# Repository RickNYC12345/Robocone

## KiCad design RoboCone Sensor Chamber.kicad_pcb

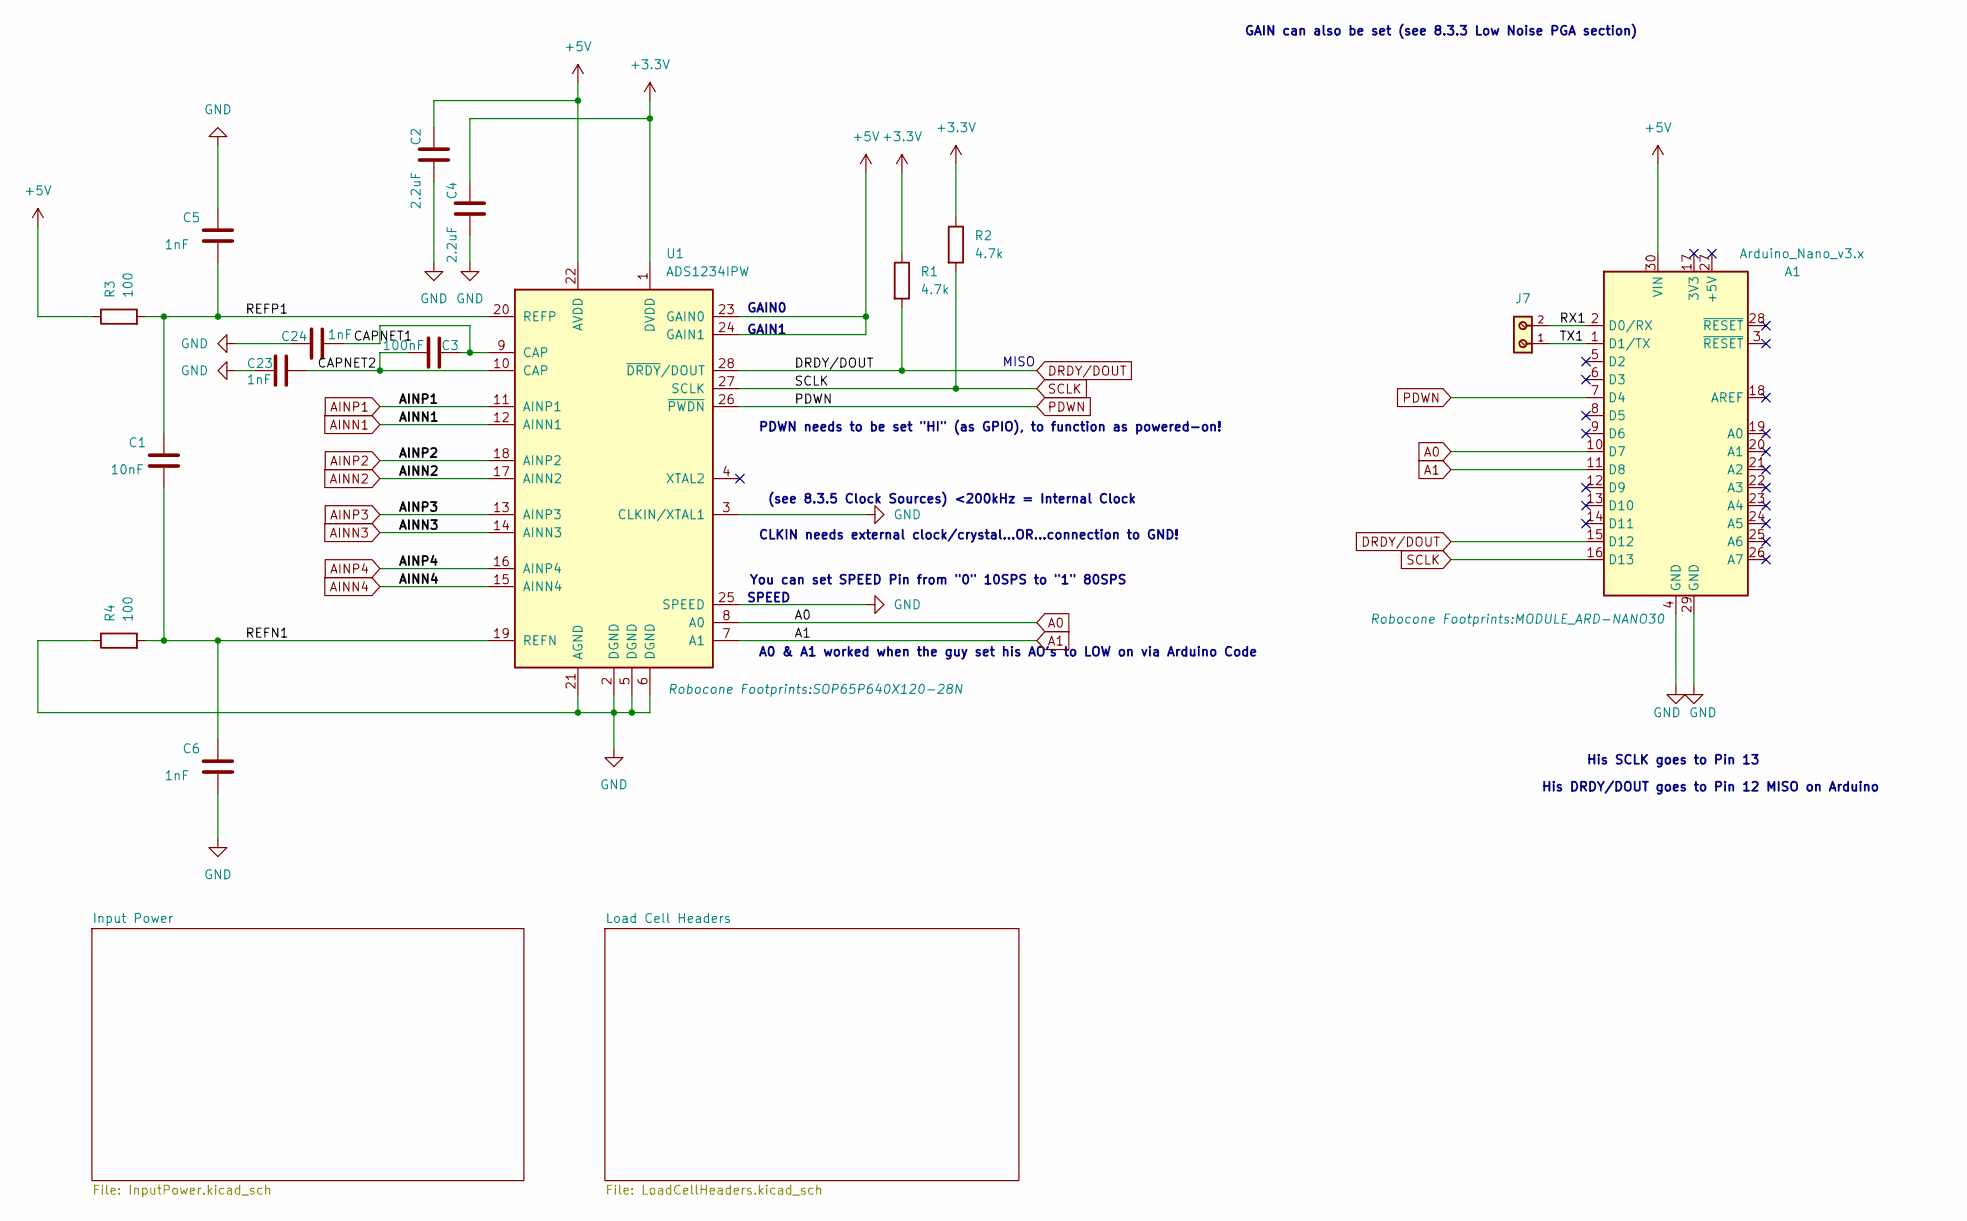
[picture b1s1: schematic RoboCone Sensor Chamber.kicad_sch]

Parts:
A1: Arduino_Nano_v3.x; MODULE_ARD-NANO30
C1: 10nF; C_0805_2012Metric_Pad1.18x1.45mm_HandSolder
C2, C4: 2.2uF; C_0805_2012Metric_Pad1.18x1.45mm_HandSolder
C3: 100nF; C_0805_2012Metric_Pad1.18x1.45mm_HandSolder
C5, C6, C23, C24: 1nF; C_0805_2012Metric_Pad1.18x1.45mm_HandSolder
J7: 691210910002; PART-NUMBER 691210910002
R1, R2: 4.7k; R_0805_2012Metric_Pad1.20x1.40mm_HandSolder
R3, R4: 100; R_0805_2012Metric_Pad1.20x1.40mm_HandSolder
U1: ADS1234IPW; SOP65P640X120-28N

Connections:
+3.3V: C4.2, R1.1, R2.1, U1.1 (DVDD); also elsewhere on the board
+5V: A1.30 (VIN), C2.2, R3.1, U1.22 (AVDD), U1.23 (GAIN0), U1.24 (GAIN1); also elsewhere on the board
/CAPNET1: C3.2, C24.2, U1.9 (CAP)
/CAPNET2: C3.1, C23.2, U1.10 (CAP)
/REFN1: C1.2, C6.1, R4.2, U1.19 (REFN)
/REFP1: C1.1, C5.2, R3.2, U1.20 (REFP)
/RX1: A1.2 (D0/RX), J7.2
/TX1: A1.1 (D1/TX), J7.1
A0: A1.10 (D7), U1.8 (A0)
A1: A1.11 (D8), U1.7 (A1)
AINN1: U1.12 (AINN1); also elsewhere on the board
AINN2: U1.17 (AINN2); also elsewhere on the board
AINN3: U1.14 (AINN3); also elsewhere on the board
AINN4: U1.15 (AINN4); also elsewhere on the board
AINP1: U1.11 (AINP1); also elsewhere on the board
AINP2: U1.18 (AINP2); also elsewhere on the board
AINP3: U1.13 (AINP3); also elsewhere on the board
AINP4: U1.16 (AINP4); also elsewhere on the board
DRDY/DOUT: A1.15 (D12), R1.2, U1.28 (~DRDY/DOUT)
GND: A1.4 (GND), A1.29 (GND), C2.1, C4.1, C5.1, C6.2, C23.1, C24.1, R4.1, U1.2 (DGND), U1.3 (CLKIN/XTAL1), U1.5 (DGND), U1.6 (DGND), U1.21 (AGND), U1.25 (SPEED); also elsewhere on the board
PDWN: A1.7 (D4), U1.26 (~PWDN)
SCLK: A1.16 (D13), R2.2, U1.27 (SCLK)

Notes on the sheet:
CLKIN needs external clock/crystal...OR...connection to GND!
GAIN0
GAIN can also be set (see 8.3.3 Low Noise PGA section)
His SCLK goes to Pin 13
GAIN1
His DRDY/DOUT goes to Pin 12 MISO on Arduino
PDWN needs to be set "HI" (as GPIO), to function as powered-on!
A0 & A1 worked when the guy set his AO's to LOW on via Arduino Code
(see 8.3.5 Clock Sources) <200kHz = Internal Clock
You can set SPEED Pin from "0" 10SPS to "1" 80SPS
SPEED
MISO

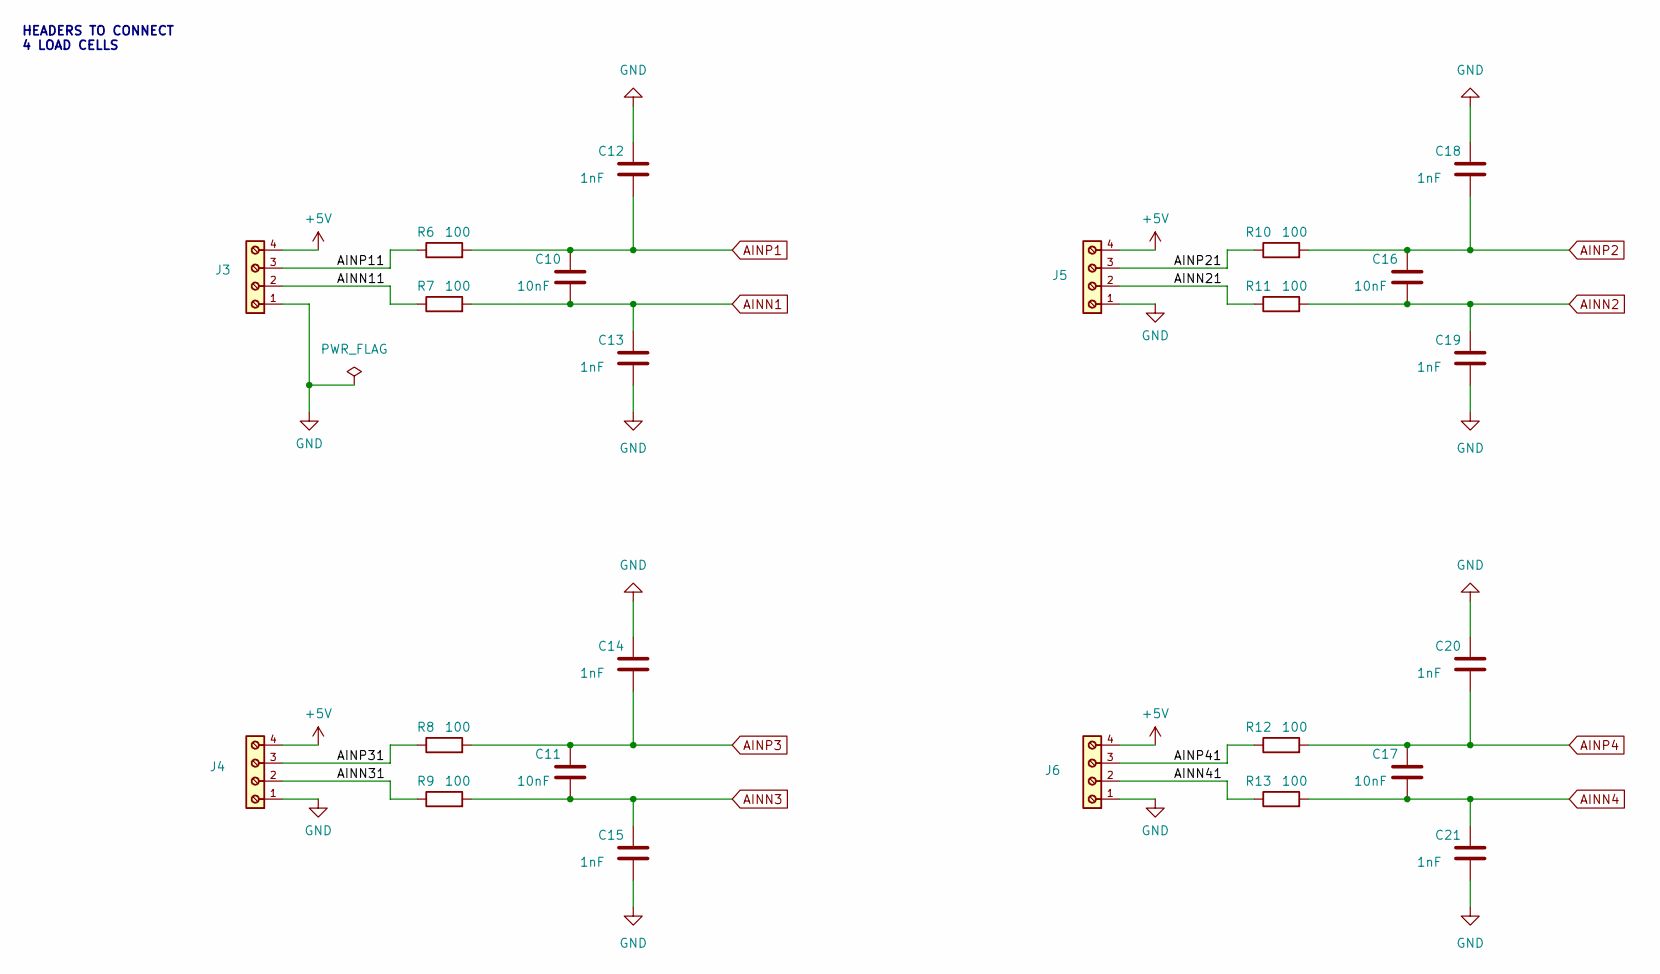
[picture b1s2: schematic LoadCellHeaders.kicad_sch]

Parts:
C10, C11, C16, C17: 10nF; C_0805_2012Metric_Pad1.18x1.45mm_HandSolder
C12, C13, C14, C15, C18, C19, C20, C21: 1nF; C_0805_2012Metric_Pad1.18x1.45mm_HandSolder
J3, J4, J5, J6: 691210910004; PART-NUMBER 691210910004
R6, R7, R8, R9, R10, R11, R12, R13: 100; R_0805_2012Metric_Pad1.20x1.40mm_HandSolder

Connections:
+5V: J3.4, J4.4, J5.4, J6.4; also elsewhere on the board
/Load Cell Headers/AINN11: J3.2, R7.1
/Load Cell Headers/AINN21: J5.2, R11.1
/Load Cell Headers/AINN31: J4.2, R9.1
/Load Cell Headers/AINN41: J6.2, R13.1
/Load Cell Headers/AINP11: J3.3, R6.1
/Load Cell Headers/AINP21: J5.3, R10.1
/Load Cell Headers/AINP31: J4.3, R8.1
/Load Cell Headers/AINP41: J6.3, R12.1
AINN1: C10.2, C13.1, R7.2; also elsewhere on the board
AINN2: C16.2, C19.1, R11.2; also elsewhere on the board
AINN3: C11.2, C15.1, R9.2; also elsewhere on the board
AINN4: C17.2, C21.1, R13.2; also elsewhere on the board
AINP1: C10.1, C12.2, R6.2; also elsewhere on the board
AINP2: C16.1, C18.2, R10.2; also elsewhere on the board
AINP3: C11.1, C14.2, R8.2; also elsewhere on the board
AINP4: C17.1, C20.2, R12.2; also elsewhere on the board
GND: C12.1, C13.2, C14.1, C15.2, C18.1, C19.2, C20.1, C21.2, J3.1, J4.1, J5.1, J6.1; also elsewhere on the board

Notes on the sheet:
HEADERS TO CONNECT 4 LOAD CELLS

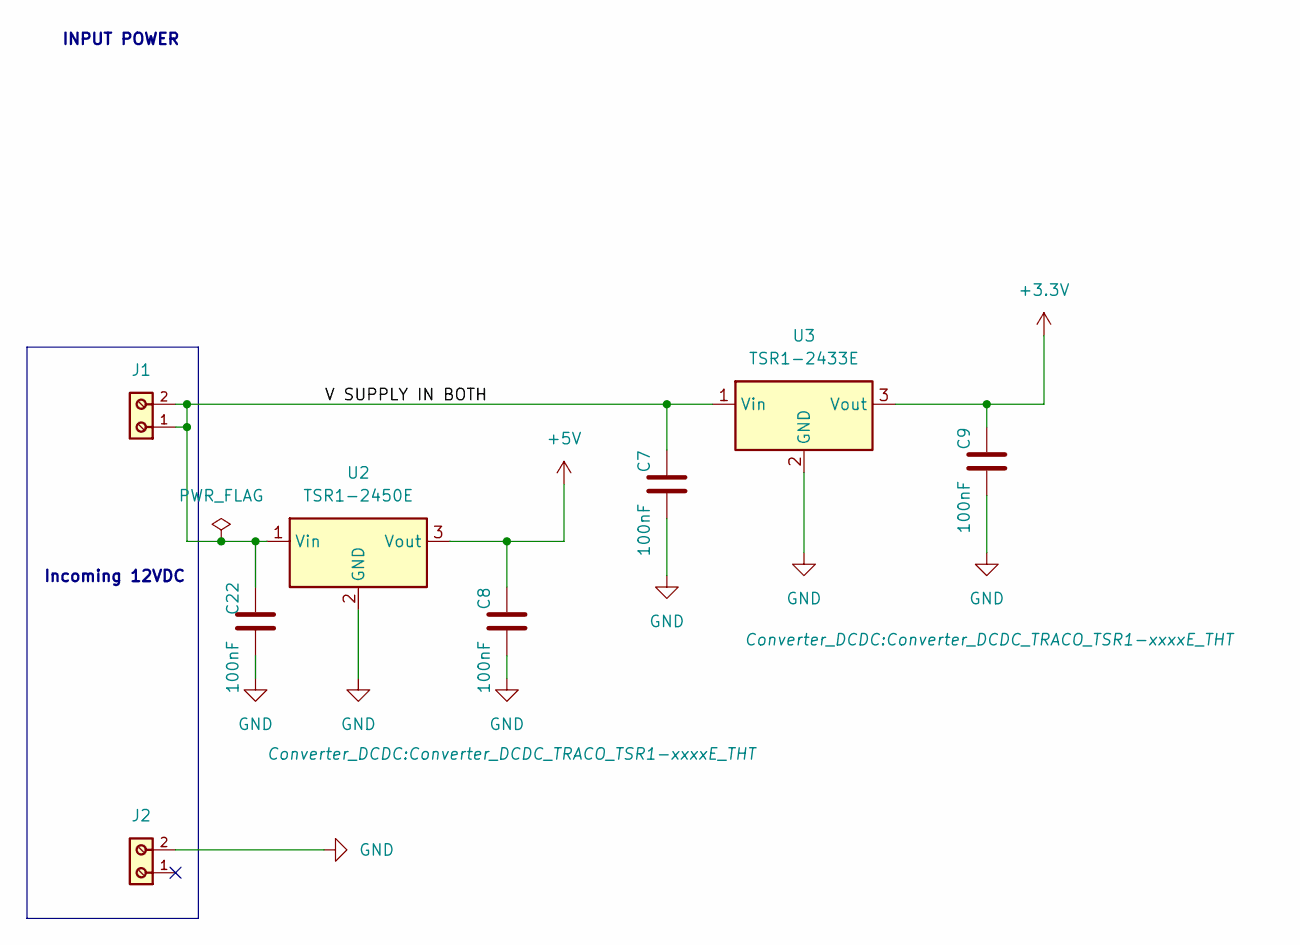
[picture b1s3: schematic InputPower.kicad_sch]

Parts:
C7, C8, C9, C22: 100nF; C_0805_2012Metric_Pad1.18x1.45mm_HandSolder
J1, J2: 691210910002; PART-NUMBER 691210910002
U2: TSR1-2450E; Converter_DCDC_TRACO_TSR1-xxxxE_THT
U3: TSR1-2433E; Converter_DCDC_TRACO_TSR1-xxxxE_THT

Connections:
+3.3V: C9.2, U3.3 (Vout); also elsewhere on the board
+5V: C8.2, U2.3 (Vout); also elsewhere on the board
/Input Power/V SUPPLY IN BOTH: C7.2, C22.2, J1.1, J1.2, U2.1 (Vin), U3.1 (Vin)
GND: C7.1, C8.1, C9.1, C22.1, J2.2, U2.2 (GND), U3.2 (GND); also elsewhere on the board

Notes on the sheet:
INPUT POWER
Incoming 12VDC

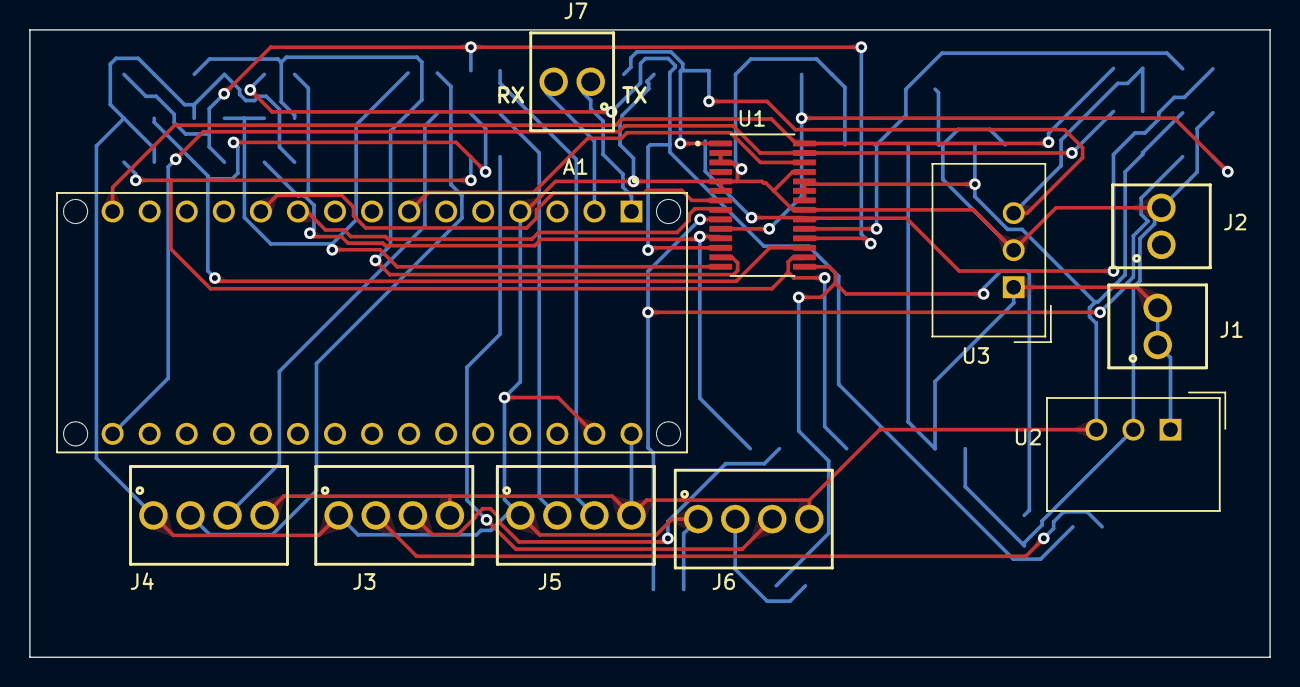
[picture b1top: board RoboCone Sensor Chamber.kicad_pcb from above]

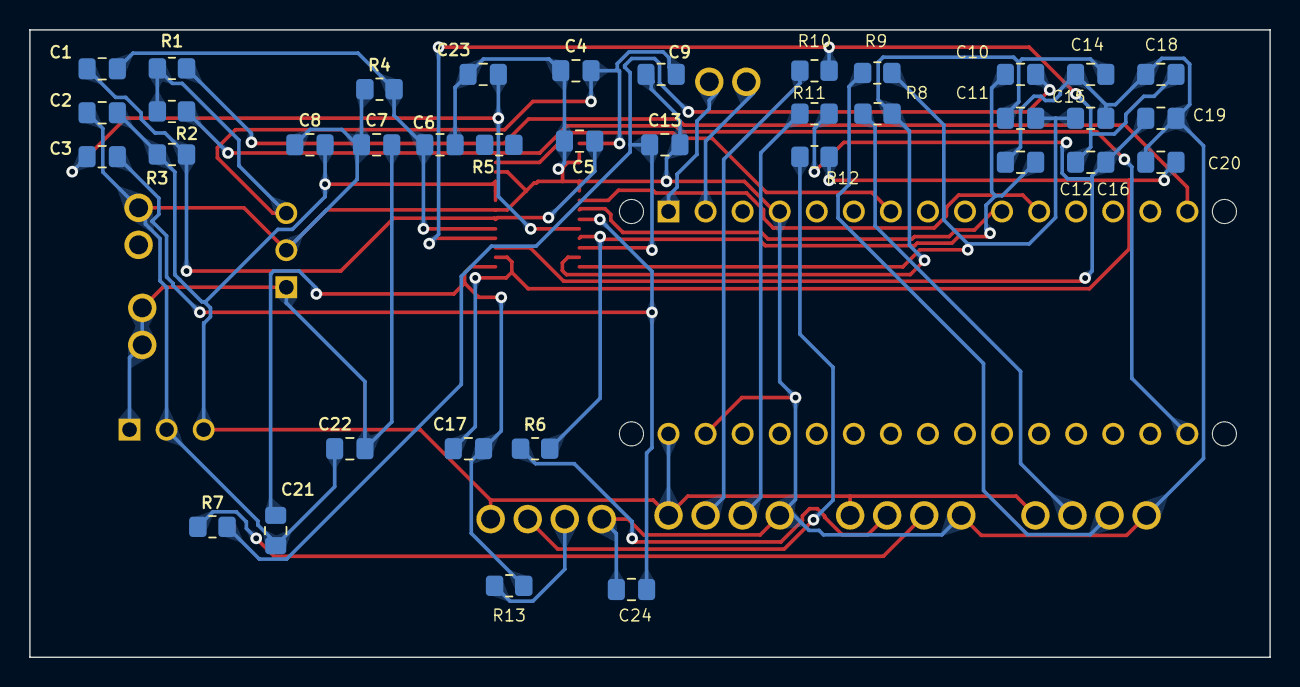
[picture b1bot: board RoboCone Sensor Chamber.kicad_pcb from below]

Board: 2 copper layers, 85.0 x 43.0 mm, 48 parts (37 on the bottom side), 31 nets.

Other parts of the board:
R5: 100k; R_0805_2012Metric_Pad1.20x1.40mm_HandSolder

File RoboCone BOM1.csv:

Reference,Value,Datasheet,Footprint,Qty,DNP,,,
A1,Arduino_Nano_v3.x,http://www.mouser.com/pdfdocs/Gravitech_Arduino_Nano3_0.pdf,Robocone Footprints:MODULE_ARD-NANO30,1,,,,
"C1,C10,C11,C16,C17",10nF,~,Capacitor_SMD:C_0805_2012Metric_Pad1.18x1.45mm_HandSolder,5,,,,
"C2,C4",2.2uF,~,Capacitor_SMD:C_0805_2012Metric_Pad1.18x1.45mm_HandSolder,2,,,,
"C3,C7,C8,C9",100nF,~,Capacitor_SMD:C_0805_2012Metric_Pad1.18x1.45mm_HandSolder,4,,,,
"C5,C6,C12,C13,C14,C15,C18,C19,C20,C21",1nF,~,Capacitor_SMD:C_0805_2012Metric_Pad1.18x1.45mm_HandSolder,10,,,,
"J1,J7",Wurth 691210910002,https://media.digikey.com/pdf/Data%20Sheets/Molex%20PDFs/A-6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,Robocone Footprints:691210910002,2,,need 1 more,,
"J2,J3,J4,J5",Wurth 691210910004,https://www.molex.com/pdm_docs/sd/022232041_sd.pdf,Robocone Footprints:691210910004,4,,,,
"R1,R2",4.7k,~,Resistor_SMD:R_0805_2012Metric_Pad1.20x1.40mm_HandSolder,2,,,,
"R3,R4,R6,R7,R8,R9,R10,R11,R12,R13",100,~,Resistor_SMD:R_0805_2012Metric_Pad1.20x1.40mm_HandSolder,10,,,,
R5,100k,~,Resistor_SMD:R_0805_2012Metric_Pad1.20x1.40mm_HandSolder,1,,,,
U1,ADS1234IPW,http://www.ti.com/lit/ds/symlink/ads1232.pdf,Robocone Footprints:SOP65P640X120-28N,1,,,,
U2,TSR1-2450E,https://www.tracopower.com/products/tsr1e.pdf,Converter_DCDC:Converter_DCDC_TRACO_TSR1-xxxxE_THT,1,,,,
U3,TSR1-2433E,https://www.tracopower.com/products/tsr1e.pdf,Converter_DCDC:Converter_DCDC_TRACO_TSR1-xxxxE_THT,1,,still need this,RS#666-4360,ordered mon.

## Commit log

2025-02-03 establishing repository
2025-02-05 Redefined nets - were not setup properly
2025-02-06 lots of PCB changes
2025-02-06 some file changes done by git?
2025-02-06 added BOM1
2025-02-06 files modified
2025-02-06 added programming code initial shells
2025-02-07 backup auto saves...
2025-02-07 test only
2025-02-07 back to normal now from test
